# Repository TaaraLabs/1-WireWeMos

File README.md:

1-Wire WeMos
============

1-Wire Shield for WeMos D1

[Official WebSite](https://taaralabs.eu/ow1)

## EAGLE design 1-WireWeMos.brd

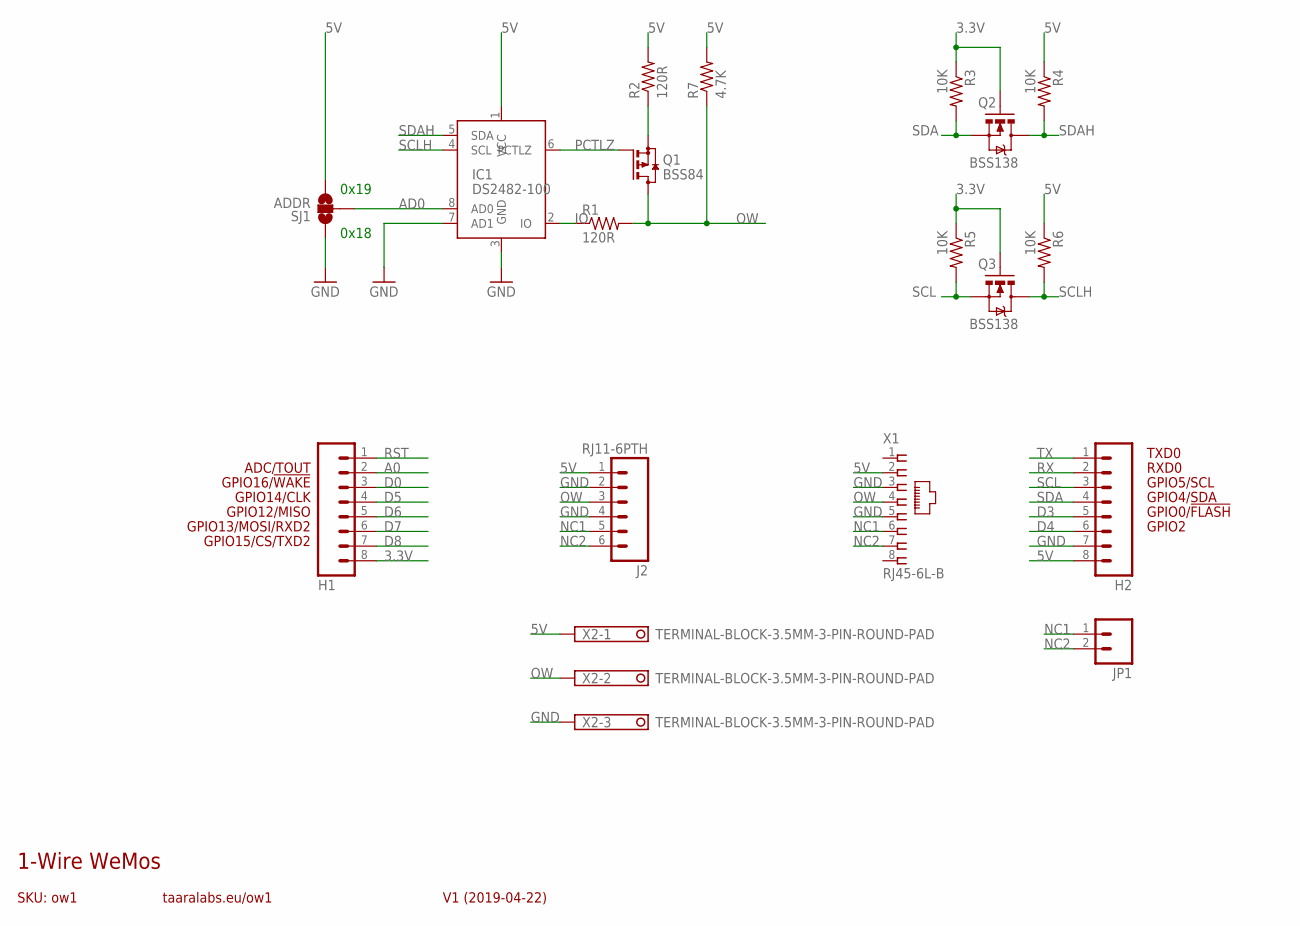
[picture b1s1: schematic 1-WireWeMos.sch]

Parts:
H1, H2: M08; 1X08
IC1: DS2482-100; SO08
J2: RJ11-6PTH; RJ11-6
JP1: M02PTH; 1X02
Q1: BSS84; SOT23
Q2, Q3: BSS138; SOT23-3
R1, R2: 120R; 0603-RES
R3, R4, R5, R6: 10K; 0603-RES
R7: 4.7K; 0603-RES
SJ1: ADDR; SJ_3_PASTE1&2
X1: RJ45-6L-B; RJ45-NO-SHIELD
X2: TERMINAL-BLOCK-3.5MM-3-PIN-ROUND-PAD; TERMINAL-BLOCK-3-PIN-3.5MM-ROUND-PAD

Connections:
3.3V: H1.8, Q2.1 (G), Q3.1 (G), R3.1, R5.1
5V: H2.8, IC1.1 (VCC), J2.1, R2.2, R4.1, R6.1, R7.2, SJ1.3, X1.2, X2.1
A0: H1.2
AD0: IC1.8 (AD0), SJ1.2
D0: H1.3
D3: H2.5
D4: H2.6
D5: H1.4
D6: H1.5
D7: H1.6
D8: H1.7
GND: H2.7, IC1.3 (GND), IC1.7 (AD1), J2.2, J2.4, SJ1.1, X1.3, X1.5, X2.3
IO: IC1.2 (IO), R1.1
NC1: J2.5, JP1.1, X1.6
NC2: J2.6, JP1.2, X1.7
OW: J2.3, Q1.3 (D), R1.2, R7.1, X1.4, X2.2
OWP: Q1.2 (S), R2.1
PCTLZ: IC1.6 (PCTLZ), Q1.1 (G)
RST: H1.1
RX: H2.2
SCL: H2.3, Q3.2 (S), R5.2
SCLH: IC1.4 (SCL), Q3.3 (D), R6.2
SDA: H2.4, Q2.2 (S), R3.2
SDAH: IC1.5 (SDA), Q2.3 (D), R4.2
TX: H2.1

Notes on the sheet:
GPIO2
GPIO0/!FLASH
GPIO12/MISO
GPIO4/SDA
GPIO5/SCL
RXD0
TXD0
GPIO13/MOSI/RXD2
GPIO14/CLK
GPIO15/CS/TXD2
GPIO16/!WAKE
SKU: ow1
1-Wire WeMos
V1 (2019-04-22)
taaralabs.eu/ow1
ADC/TOUT
0x18
0x19

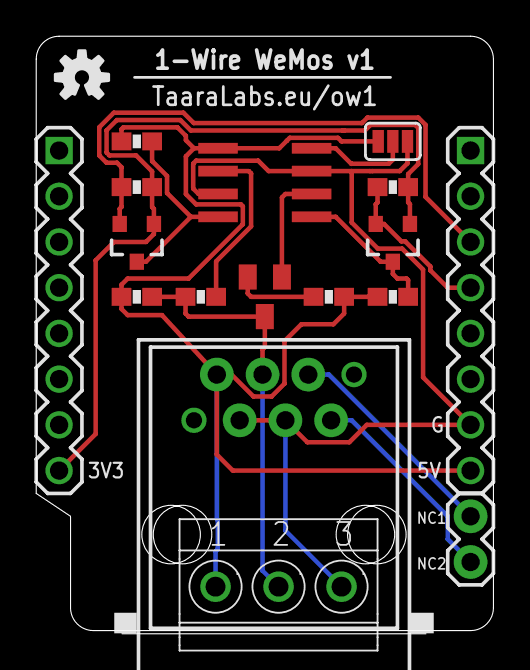
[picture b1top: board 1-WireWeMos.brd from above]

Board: 2 copper layers, 25.4 x 33.2 mm, 20 parts (1 on the bottom side), 14 nets.

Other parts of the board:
U$1, U$2: OSHW-LOGO-S

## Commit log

2018-04-22 initial upload
2018-04-22 README.md added
2018-04-22 pictures of schematic and board added
2018-04-22 mockup picture updated
2018-04-22 board layout picture updated
2018-04-22 R5 name deleted
2018-04-23 year number fixed
2018-11-24 added product photos
2018-11-24 added gerbers
2025-02-22 ESPHome example

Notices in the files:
parts and their libraries:
freetronics-original: Licensing: CC v3.0 Share-Alike You are welcome to use this library for commercial purposes.
